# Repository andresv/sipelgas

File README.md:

## Sipelgas

ANT based sensors using TI MSP430FR5728 microcontroller and Nordic Semiconductor nRF24AP2-1CH radiochip that runs ANT protocol stack.

## LICENSE
### Hardware
This work is licensed under version 3.0 of the Creative Commons CC-BY-SA license.
http://creativecommons.org/licenses/by-sa/3.0/

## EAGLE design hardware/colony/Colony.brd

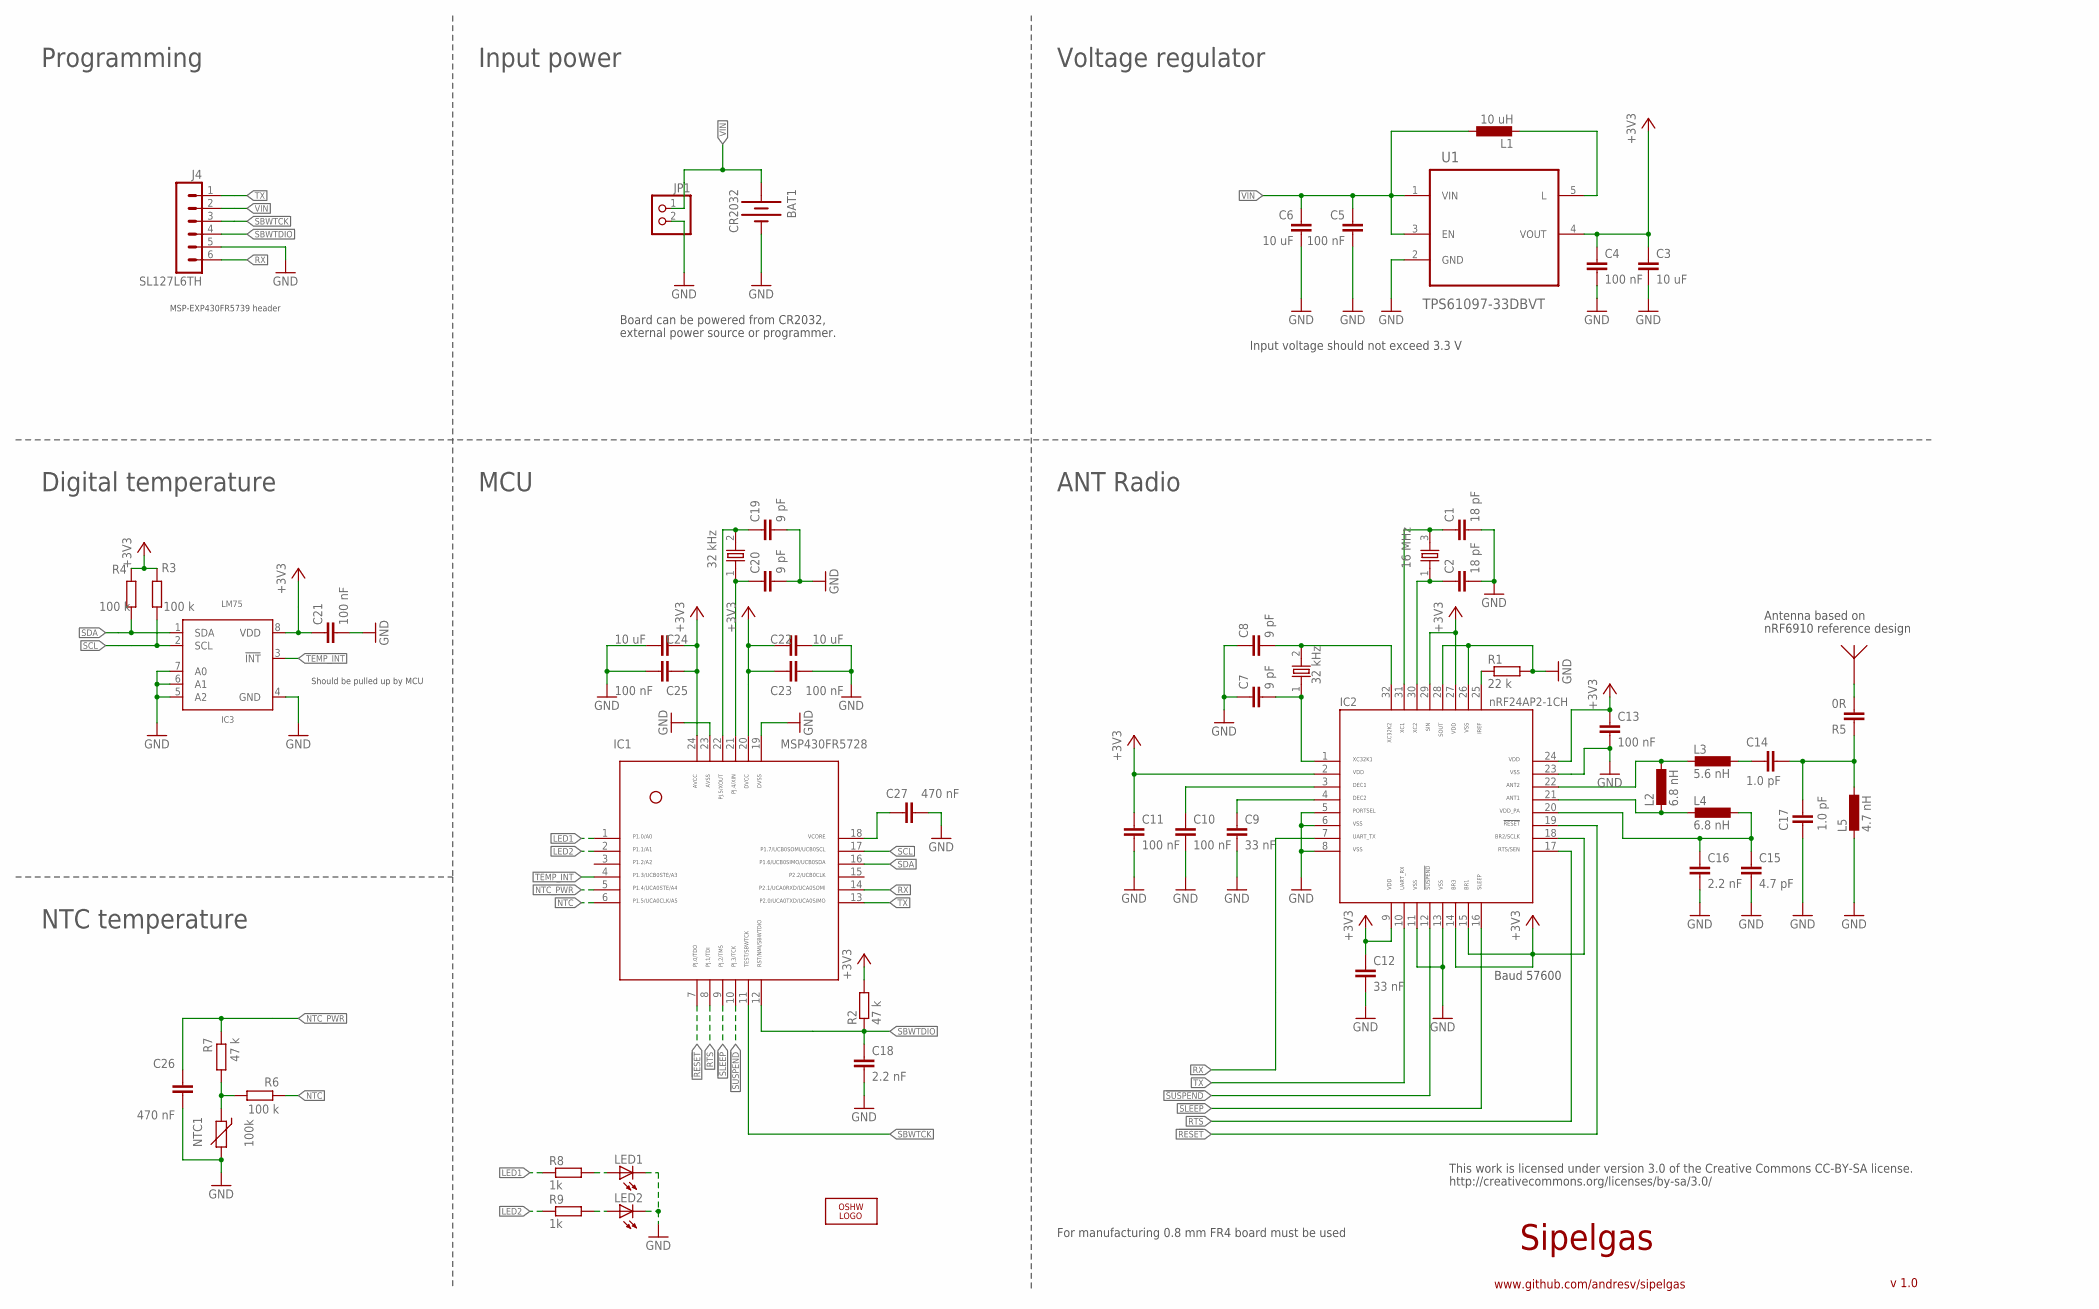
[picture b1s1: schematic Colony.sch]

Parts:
BAT1: CR2032; BATTCON_20MM
C1, C2: 18 pF; C0402
C3, C6, C22, C24: 10 uF; C0402
C4, C5, C10, C11, C13, C21, C23, C25: 100 nF; C0402
C7, C8, C19, C20: 9 pF; C0402
C9, C12: 33 nF; C0402
C14, C17: 1.0 pF; C0402
C15: 4.7 pF; C0402
C16, C18: 2.2 nF; C0402
C26, C27: 470 nF; C0402
IC1: MSP430FR5728; QFN-24
IC2: nRF24AP2-1CH; QFN-32
IC3: LM75; MSOP8
J4: SL127L6TH; SL127L6_MPE
JP1: PINHD-1X2; 1X02
L1: 10 uH; L0805
L2, L4: 6.8 nH; L0402
L3: 5.6 nH; L0402
L5: 4.7 nH; L0402
LED1, LED2: LEDCHIP-LED0603; CHIP-LED0603
LOGO1: OSHW_LOGO_6MILX0100-NT; OSHW_6X100_NOTEXT
NTC1: 100k; RS-2,5
Q1: 16 MHz; CTS402_3.2X2.5
Q2, Q3: 32 kHz; ABS07
R1: 22 k; R0402
R2, R7: 47 k; R0402
R3, R4, R6: 100 k; R0402
R5: 0R; C0201
R8, R9: 1k; R0402
U1: TPS61097-33DBVT; SOT95P280X145-5N
U$1: NRF6910-ANTENNA; NRF6910

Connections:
!RESET: IC1.7, IC2.19
!SLEEP: IC1.9, IC2.16
!SUSPEND: IC1.10, IC2.12
+3V3: C3.1, C4.1, C11.1, C12.1, C13.1, C21.1, C22.1, C23.1, C24.1, C25.1, IC1.20, IC1.24, IC2.2, IC2.9, IC2.14, IC2.15, IC2.18, IC2.24, IC2.27, IC2.29, IC3.8 (VDD), R2.2, R3.2, R4.2, U1.4 (VOUT)
ANT: C14.2, C17.1, L5.1, R5.1
GND: BAT1.2 (-), C1.2, C2.2, C3.2, C4.2, C5.2, C6.2, C7.1, C8.1, C9.2, C10.2, C11.2, C12.2, C13.2, C15.2, C16.2, C17.2, C18.2, C19.2, C20.2, C21.2, C22.2, C23.2, C24.2, C25.2, C26.2, C27.2, IC1.19, IC1.23, IC2.5, IC2.6, IC2.8, IC2.11, IC2.13, IC2.23, IC2.26, IC2.28, IC3.4 (GND), IC3.5 (A2), IC3.6 (A1), IC3.7 (A0), J4.5, JP1.2, L5.2, LED1.C, LED2.C, NTC1.2, R1.2, U1.2 (GND)
LED1: IC1.1, R8.1
LED2: IC1.2, R9.1
unnamed: C2.1, IC2.30, Q1.1
unnamed: C1.1, IC2.31, Q1.3 (2)
unnamed: L1.2, U1.5 (L)
unnamed: IC2.25, R1.1
unnamed: C9.1, IC2.4
unnamed: C7.2, IC2.1, Q3.1
unnamed: C8.2, IC2.32, Q3.2
unnamed: C10.1, IC2.3
unnamed: C20.1, IC1.21, Q2.1
unnamed: C19.1, IC1.22, Q2.2
unnamed: NTC1.1, R6.1, R7.1
unnamed: C27.1, IC1.18
unnamed: LED1.A, R8.2
unnamed: R5.2, U$1.P$1
unnamed: LED2.A, R9.2
unnamed: IC2.22, L2.1, L3.2
unnamed: IC2.21, L2.2, L4.2
unnamed: C15.1, C16.1, IC2.20, L4.1
unnamed: C14.1, L3.1
NTC: IC1.6, R6.2
NTC_PWR: C26.1, IC1.5, R7.2
RTS: IC1.8, IC2.17
RX: IC1.14, IC2.7, J4.6
SBWTCK: IC1.11, J4.3
SBWTDIO: C18.1, IC1.12, J4.4, R2.1
SCL: IC1.17, IC3.2 (SCL), R3.1
SDA: IC1.16, IC3.1 (SDA), R4.1
TEMP_INT: IC1.4, IC3.3 (!INT)
TX: IC1.13, IC2.10, J4.1
VIN: BAT1.1 (+), C5.1, C6.1, J4.2, JP1.1, L1.1, U1.1 (VIN), U1.3 (EN)

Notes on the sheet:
Sipelgas
www.github.com/andresv/sipelgas
Input voltage should not exceed 3.3 V
Board can be powered from CR2032,
Baud 57600
external power source or programmer.
ANT Radio
MCU
Digital temperature
NTC temperature
Programming
Input power
Voltage regulator
MSP-EXP430FR5739 header
Should be pulled up by MCU
Antenna based on
nRF6910 reference design
For manufacturing 0.8 mm FR4 board must be used
v 1.0
This work is licensed under version 3.0 of the Creative Commons CC-BY-SA license.
http://creativecommons.org/licenses/by-sa/3.0/

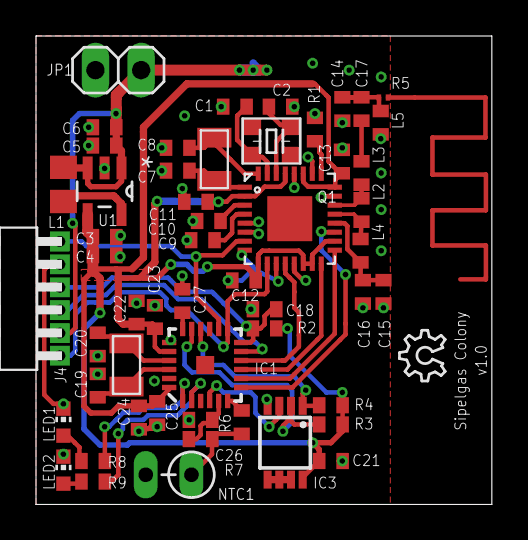
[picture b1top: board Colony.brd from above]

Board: 2 copper layers, 25.3 x 26.0 mm, 56 parts (1 on the bottom side), 38 nets.

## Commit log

2012-07-18 Added library files.
2012-07-18 Added first colony board schematic and layout.
2012-07-18 Added hardware license file.
2012-07-18 Added hardware license information to readme.
2013-03-03 Connected nRF24AP2-1CH pad to GND.
